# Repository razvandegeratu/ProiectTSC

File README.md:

Descrierea Funcționalității Hardware
Module și Interfețe

    Microcontroller: nRF52840 gestionează procesarea centrală.

    Display E-Paper: Comunică prin interfața SPI. S-a ales acest tip de ecran datorită consumului de energie zero în stare statică.

    Senzor IMU: Conectat prin I2C, utilizat pentru detectarea mișcării și orientării.

    Sistem de alimentare: Include un circuit de încărcare pentru bateria Li-Po și convertoare DC/DC pentru a asigura pragurile de tensiune de 3.3V necesare componentelor digitale.

    Interfață Utilizator: Trei butoane mecanice pentru navigare și un motor de vibrații pentru notificări haptice.

## Bill of Materials (BOM)

|Component|JLC Part #|Package|Description|Datasheet|
| :--- | :--- | :--- | :--- | :--- |
|C23, C27, C34, C42|[C21012218](https://www.lcsc.com/product-detail/C21012218.html)|-|Check availability|[datasheet](https://jlc-prod-smt.oss-eu-central-1.aliyuncs.com/smtDataManualFile/8603520985945550848-C21012218.pdf?response-content-disposition=attachment%3B%20filename%3DC21012218.pdf%3B%20filename%2A%3DUTF-8%27%27C21012218.pdf&x-oss-date=20260407T205848Z&x-oss-expires=1800&x-oss-security-token=CAISgAN1q6Ft5B2yfSjIr5r9Dd2HhJt1xpCRZnzhgHQ0Psp9nrTKiTz2IHhMdHJsAOodtv0%2FmmhT6PkclqRLcbhpcmfjV%2BZHzLB8qYoRtS1%2F4J7b16cNrbH4M4H6aXeirtuwDsz9SNTCALjPD3nPii50x5bjaDymRCbLGJaViJlhHLN1Ow6jdmhpCctxLAlvo9NgFxm3D%2Fu2NQPwiWf9FVdhvhEG6Vly8qOi2MaRmFy8yFTx0b0SvJ%2BjYMrmPctoN9JnSdC5mfdzau3a1TJ84gRD0a5wkaVA1zbDs5bfISEIuUzebreLqY03dV4mOvdqIcMe8qigz88fk%2FfIioH6xyxKOexoSCnFTOiiupCcQLPyao9jLu6iayqViY7QaIOTqQohZmkAMwVOasAsI3Ngh4zF97Qt0cVNkXO9gWfLI8DtuMleWoolCMBMoNHD0eS19jklBdzSlusJRAJJUVBflCeKEaRNSAd3WGhEfM2%2BBt4QT30w5N2u00S8OSMIfXAg5qKWD5sagAGsz%2FZUSUxHdlmxVPmipF%2FTcZWs78wlHh10XRuVSQAFwkjbrT5Hik%2Bt6g43igoBe9p%2FcAdU6beRw%2F0OV8Ul08RsL45K5wTZwHFsbzFcwqB3eAqV0VruhFdx%2FHGC73AK3f%2BS3e6Qh1%2F1xoEQbmetO%2F%2BEcdyt%2BmwKiZrCa5Agq9keuCAA&x-oss-signature-version=OSS4-HMAC-SHA256&x-oss-credential=STS.NYHFg3iDTqRzdZPdta2EQqqak%2F20260407%2Feu-central-1%2Foss%2Faliyun_v4_request&x-oss-signature=20ddec61a1b664f2d44439cb342bbd932d8702b658f2816e0dfb7eb77563430a)|
|R2_EP_DR, R9, R_PWR_EPD|[C3920633](https://www.lcsc.com/product-detail/C3920633.html)|0201|7.68k 0201 Thin Film Surface Mount Fixed Resistor +/-0.5% 0.031W CPF0201D7K68C1|[datasheet](https://wmsc.lcsc.com/wmsc/upload/file/pdf/v2/lcsc/2404081048_TE-Connectivity-CPF0201B511RE1_C3920633.pdf)|
|C1-EP-DR|[C9900156064](https://www.lcsc.com/product-detail/C9900156064.html)|201|Generic chip capacitor|[datasheet](https://ds.yuden.co.jp/TYCOMPAS/or/download?pn=MLAST063SCG681JFNA01&fileType=CA)|
|C2-EP-DR|[C9900156064](https://www.lcsc.com/product-detail/C9900156064.html)|201|Generic chip capacitor|[datasheet](https://ds.yuden.co.jp/TYCOMPAS/or/download?pn=MLAST063SCG681JFNA01&fileType=CA)|
|C11|[C9900156064](https://www.lcsc.com/product-detail/C9900156064.html)|201|Generic chip capacitor|[datasheet](https://ds.yuden.co.jp/TYCOMPAS/or/download?pn=MLAST063SCG681JFNA01&fileType=CA)|
|C24, C39|[C9900179830](https://www.lcsc.com/product-detail/C9900179830.html)|402|0402 (1005 Metric)|N/A|
|L2|[C12669](https://www.lcsc.com/product-detail/C12669.html)|402|Generic chip inductor|[datasheet](https://www.lcsc.com/datasheet/lcsc_datasheet_2304140030_Murata-Electronics-LQG15HS27NJ02D_C12669.pdf)|
|C1, C2, C17, C18|[C9900156064](https://www.lcsc.com/product-detail/C9900156064.html)|201|Generic chip capacitor|[datasheet](https://ds.yuden.co.jp/TYCOMPAS/or/download?pn=MLAST063SCG681JFNA01&fileType=CA)|
|L3|[C12669](https://www.lcsc.com/product-detail/C12669.html)|402|Generic chip inductor|[datasheet](https://www.lcsc.com/datasheet/lcsc_datasheet_2304140030_Murata-Electronics-LQG15HS27NJ02D_C12669.pdf)|
|C3, C4|[C9900156064](https://www.lcsc.com/product-detail/C9900156064.html)|201|Generic chip capacitor|[datasheet](https://ds.yuden.co.jp/TYCOMPAS/or/download?pn=MLAST063SCG681JFNA01&fileType=CA)|
|SJ1|N/A|Solder Jumper (Copper feature - leave open)|SMD solder JUMPER|N/A|
|C29, C30, C31, C32, C37, C38|[C3920633](https://www.lcsc.com/product-detail/C3920633.html)|0201|7.68k 0201 Thin Film Surface Mount Fixed Resistor +/-0.5% 0.031W CPF0201D7K68C1|[datasheet](https://wmsc.lcsc.com/wmsc/upload/file/pdf/v2/lcsc/2404081048_TE-Connectivity-CPF0201B511RE1_C3920633.pdf)|
|EPD_C1, EPD_C2, EPD_C6, EPD_C7, EPD_C8, EPD_C9, EPD_C10, EPD_C11, EPD_C12|[C9900156064](https://www.lcsc.com/product-detail/C9900156064.html)|201|Generic chip capacitor|[datasheet](https://ds.yuden.co.jp/TYCOMPAS/or/download?pn=MLAST063SCG681JFNA01&fileType=CA)|
|SW_DN, SW_ENT, SW_UP|[C569760](https://www.lcsc.com/product-detail/C569760.html)|SMD,3.9x2.9mm|-40℃~+85℃ 1.6N 1.6mm 15V 2.9mm 20mA 3.9mm 500,000 Cycles IP67 J-Lead Rectangular Button SPST Surface Mount,Vertical White With Bracket SMD,3.9x2.9mm Tactile Switches ROHS|[datasheet](https://wmsc.lcsc.com/wmsc/upload/file/pdf/v2/lcsc/2301111010_PANASONIC-EVPAKE31A_C569760.pdf)|
|Q1|[C2564](https://www.lcsc.com/product-detail/C2564.html)|TO-220AB|-55℃~+175℃ 1 P-Channel 180nC@10V 200W 20mΩ@10V 3.4nF 4V 55V 640pF 74A P-Channel TO-220AB MOSFETs ROHS|[datasheet](https://www.lcsc.com/datasheet/lcsc_datasheet_1809041724_Infineon-Technologies-IRF4905PBF_C2564.pdf)|
|C25, C33|[C9900179830](https://www.lcsc.com/product-detail/C9900179830.html)|402|0402 (1005 Metric)|N/A|
|ANT1|[C2917717](https://www.lcsc.com/product-detail/C2917717.html)|1206|-45℃~+125℃ 0.5dBi 1.3mm 1.6mm 100MHz 2.45GHz 2W 3.2mm 50Ω Patch Antenna 1206 Antennas ROHS|[datasheet](https://www.lcsc.com/datasheet/lcsc_datasheet_2404021210_Johanson-Dielectrics-2450AT18B100E_C2917717.pdf)|
|L1|[C12669](https://www.lcsc.com/product-detail/C12669.html)|402|Generic chip inductor|[datasheet](https://www.lcsc.com/datasheet/lcsc_datasheet_2304140030_Murata-Electronics-LQG15HS27NJ02D_C12669.pdf)|
|X2|[C32346](https://www.lcsc.com/product-detail/C32346.html)|SMD3215-2P|-40℃~+85℃ 12.5pF 32.768kHz 70kΩ Crystal Oscillator ±20ppm SMD3215-2P Crystals ROHS|[datasheet](https://www.lcsc.com/datasheet/lcsc_datasheet_2404180925_Seiko-Epson-Q13FC13500004_C32346.pdf)|
|X1|[C9009](https://www.lcsc.com/product-detail/C9009.html)|SMD3225-4P|-40℃~+85℃ 12pF 32MHz Crystal Oscillator ±10ppm ±20ppm SMD3225-4P Crystals ROHS|[datasheet](https://www.lcsc.com/datasheet/lcsc_datasheet_2403291504_YXC-Crystal-Oscillators-X322532MOB4SI_C9009.pdf)|
|R17, R18|[C3920633](https://www.lcsc.com/product-detail/C3920633.html)|0201|7.68k 0201 Thin Film Surface Mount Fixed Resistor +/-0.5% 0.031W CPF0201D7K68C1|[datasheet](https://wmsc.lcsc.com/wmsc/upload/file/pdf/v2/lcsc/2404081048_TE-Connectivity-CPF0201B511RE1_C3920633.pdf)|
|C43|[C9900156064](https://www.lcsc.com/product-detail/C9900156064.html)|201|Generic chip capacitor|[datasheet](https://ds.yuden.co.jp/TYCOMPAS/or/download?pn=MLAST063SCG681JFNA01&fileType=CA)|
|R1_EP_DR|[C3920633](https://www.lcsc.com/product-detail/C3920633.html)|0201|7.68k 0201 Thin Film Surface Mount Fixed Resistor +/-0.5% 0.031W CPF0201D7K68C1|[datasheet](https://wmsc.lcsc.com/wmsc/upload/file/pdf/v2/lcsc/2404081048_TE-Connectivity-CPF0201B511RE1_C3920633.pdf)|
|C6, C14, C20, C21|[C9900156064](https://www.lcsc.com/product-detail/C9900156064.html)|201|Generic chip capacitor|[datasheet](https://ds.yuden.co.jp/TYCOMPAS/or/download?pn=MLAST063SCG681JFNA01&fileType=CA)|
|EPD_C5|[C9900156064](https://www.lcsc.com/product-detail/C9900156064.html)|201|Generic chip capacitor|[datasheet](https://ds.yuden.co.jp/TYCOMPAS/or/download?pn=MLAST063SCG681JFNA01&fileType=CA)|
|D3|[C2969755](https://www.lcsc.com/product-detail/C2969755.html)|SOT-23-6L|Low Cap. ESD Protection Auto SOT-23-6 STMicroelectronics USBLC6-2SC6Y, Dual Uni-Directional TVS Diode Array, 6-Pin SOT-23|[datasheet](https://wmsc.lcsc.com/wmsc/upload/file/pdf/v2/lcsc/2211080730_STMicroelectronics-USBLC6-2SC6Y_C2969755.pdf)|
|C16|[C9900156064](https://www.lcsc.com/product-detail/C9900156064.html)|201|Generic chip capacitor|[datasheet](https://ds.yuden.co.jp/TYCOMPAS/or/download?pn=MLAST063SCG681JFNA01&fileType=CA)|
|J1|[C122434](https://www.lcsc.com/product-detail/C122434.html)|SMD,P=0.5mm,Surface Mount，Right Angle|FFC & FPC Connectors 0.5mm FPC RA SMT Dual Contact 24Ckt|[datasheet](https://www.molex.com/content/dam/molex/molex-dot-com/products/automated/en-us/salesdrawingpdf/503/503480/5034802400_sd.pdf)|
|R1_USB, R2_USB|[C3920633](https://www.lcsc.com/product-detail/C3920633.html)|0201|7.68k 0201 Thin Film Surface Mount Fixed Resistor +/-0.5% 0.031W CPF0201D7K68C1|[datasheet](https://wmsc.lcsc.com/wmsc/upload/file/pdf/v2/lcsc/2404081048_TE-Connectivity-CPF0201B511RE1_C3920633.pdf)|
|L5|[C1329646](https://www.lcsc.com/product-detail/C1329646.html)|SMD,4.8x4.8mm|1.6A 1.6A 4.7uH 41.4mΩ AEC-Q200 ±30% SMD,4.8x4.8mm Power Inductors ROHS|[datasheet](https://wmsc.lcsc.com/wmsc/upload/file/pdf/v2/lcsc/2304140030_BOURNS-SRR4828A-4R7Y_C1329646.pdf)|
|C9|[C9900156064](https://www.lcsc.com/product-detail/C9900156064.html)|201|Generic chip capacitor|[datasheet](https://ds.yuden.co.jp/TYCOMPAS/or/download?pn=MLAST063SCG681JFNA01&fileType=CA)|
|IC3|[C189517](https://www.lcsc.com/product-detail/C189517.html)|LGA-12(2x2)|Accelerometers Triaxial low-g 12bit Acceleration Sensor|[datasheet](https://www.lcsc.com/datasheet/C189517.pdf)|
|R5, R7, R8|[C3920633](https://www.lcsc.com/product-detail/C3920633.html)|0201|7.68k 0201 Thin Film Surface Mount Fixed Resistor +/-0.5% 0.031W CPF0201D7K68C1|[datasheet](https://wmsc.lcsc.com/wmsc/upload/file/pdf/v2/lcsc/2404081048_TE-Connectivity-CPF0201B511RE1_C3920633.pdf)|
|IC1|[C3682423](https://www.lcsc.com/product-detail/C3682423.html)|DSBGA-8(1.1x1.6)|Charger IC Lithium Ion/Polymer, Lithium Iron Phosphate 8-DSBGA (1.6x1.1)|[datasheet](https://www.ti.com/cn/lit/ds/symlink/bq25180.pdf?ts=1775594237116)|
|IC2|[C81079](https://www.lcsc.com/product-detail/C81079.html)|DSBGA-9|Haptic Driver for ERM/LRA with Built-In Library and Smart Loop Architecture|[datasheet](https://www.ti.com/cn/lit/gpn/drv2605)|
|C5, C7, C8, C12, C19|[C9900156064](https://www.lcsc.com/product-detail/C9900156064.html)|201|Generic chip capacitor|[datasheet](https://ds.yuden.co.jp/TYCOMPAS/or/download?pn=MLAST063SCG681JFNA01&fileType=CA)|
|C15|[C9900156064](https://www.lcsc.com/product-detail/C9900156064.html)|201|Generic chip capacitor|[datasheet](https://ds.yuden.co.jp/TYCOMPAS/or/download?pn=MLAST063SCG681JFNA01&fileType=CA)|
|R_TYPE_SEL|[C3920633](https://www.lcsc.com/product-detail/C3920633.html)|0201|7.68k 0201 Thin Film Surface Mount Fixed Resistor +/-0.5% 0.031W CPF0201D7K68C1|[datasheet](https://wmsc.lcsc.com/wmsc/upload/file/pdf/v2/lcsc/2404081048_TE-Connectivity-CPF0201B511RE1_C3920633.pdf)|
|L7|[C5832368](https://www.lcsc.com/product-detail/C5832368.html)|1008|13mΩ 470nH 6.5A 7.5A ±20% 1008 Power Inductors ROHS|[datasheet](https://wmsc.lcsc.com/wmsc/upload/file/pdf/v2/lcsc/2306021632_cjiang--Changjiang-Microelectronics-Tech-FTC252012SR47MBCA_C5832368.pdf)|
|TP (Test Pads)|N/A|N/A|Test pad|N/A|
|J4|[C709357](https://www.lcsc.com/product-detail/C709357.html)|SMD|-40℃~+85℃ 1 10,000 cycles 16P 30V 3A 7.81mm Female Surface Mount, Right Angle Type-C SMD USB Connectors ROHS|[datasheet](https://www.lcsc.com/datasheet/lcsc_datasheet_2404191039_Shenzhen-Kinghelm-Elec-KH-TYPE-C-16P_C709357.pdf)|
|U2|[C2682616](https://www.lcsc.com/product-detail/C2682616.html)|DFN-8-EP(2x2)|-40℃~+85℃ 1 2.5V~4.5V 3uA I2C Lithium Battery DFN-8-EP(2x2) Battery Management ROHS|[datasheet](https://www.lcsc.com/datasheet/lcsc_datasheet_2410121738_Analog-Devices-Inc--Maxim-Integrated-MAX17048G-T10_C2682616.pdf)|
|D2, D4, D5|[C82046](https://www.lcsc.com/product-detail/C82046.html)|SOD-123|ON SEMICONDUCTOR - MBR0530 - DIODE, SCHOTTKY, 0.5A, 30V, SOD-123|[datasheet](https://www.lcsc.com/datasheet/lcsc_datasheet_2304140030_onsemi-MBR0530T1G_C82046.pdf)|
|C10, C13, C22|[C9900156064](https://www.lcsc.com/product-detail/C9900156064.html)|201|Generic chip capacitor|[datasheet](https://ds.yuden.co.jp/TYCOMPAS/or/download?pn=MLAST063SCG681JFNA01&fileType=CA)|
|U1|[C3606653](https://www.lcsc.com/product-detail/C3606653.html)|QFN-48(6x6)|nRF52840|[datasheet](https://www.lcsc.com/datasheet/C3606653.pdf)|
|IC9|[C7065276](https://www.lcsc.com/product-detail/C7065276.html)|WLCSP-15B(2.3x1.4)|Buck-Boost Regulator Positive Output Step-Up/Step-Down I2C DC-DC Controller IC 15-WL-CSP (BSC) (1.4x2.3)|[datasheet](https://wmsc.lcsc.com/wmsc/upload/file/pdf/v2/lcsc/2312271436_Richtek-Tech-RT6160AWSC_C7065276.pdf)|
|Q3|[C469327](https://www.lcsc.com/product-detail/C469327.html)|SOT-323|MOSFET N-Ch 30V 1.5A TrenchFET SC70 Vishay Si1308EDL-T1-GE3 N-channel MOSFET Transistor, 1.5 A, 30 V, 3-Pin SC-70|[datasheet](https://www.lcsc.com/datasheet/lcsc_datasheet_1912202016_Vishay-Intertech-SI1308EDL-T1-GE3_C469327.pdf)|
|J2|[C90533](https://www.lcsc.com/product-detail/C90533.html)|P=1mm|CABLE ADAPTER 6 POS|[datasheet](https://wmsc.lcsc.com/wmsc/upload/file/pdf/v2/lcsc/1810141506_LX-FFC6P1-0mm7CM_C90533.pdf)|

5. Design Log și Decizii Tehnice

    PCB Stackup: Placa are o grosime de 1mm
    Plan de masă: S-au implementat planuri de masă pe ambele straturi (Top și Bottom) legate prin Via Stitching pentru a minimiza zgomotul electromagnetic, în special în zona circuitului radio.

    Antenă: Zona de sub antenă a fost decupată complet de planul de masă pe toate straturile pentru a asigura performanța optimă a semnalului BLE.

    Erori DRC acceptate: S-au ignorat erorile de tip "Dimension" la butoane și mufa USB-C deoarece acestea sunt necesare pentru alinierea mecanică cu carcasa, conform specificațiilor.

    Componente: Toate rezistențele și condensatoarele de decuplare (100nF) au fost plasate în capsulă 0201 cât mai aproape de pinii IC-urilor.

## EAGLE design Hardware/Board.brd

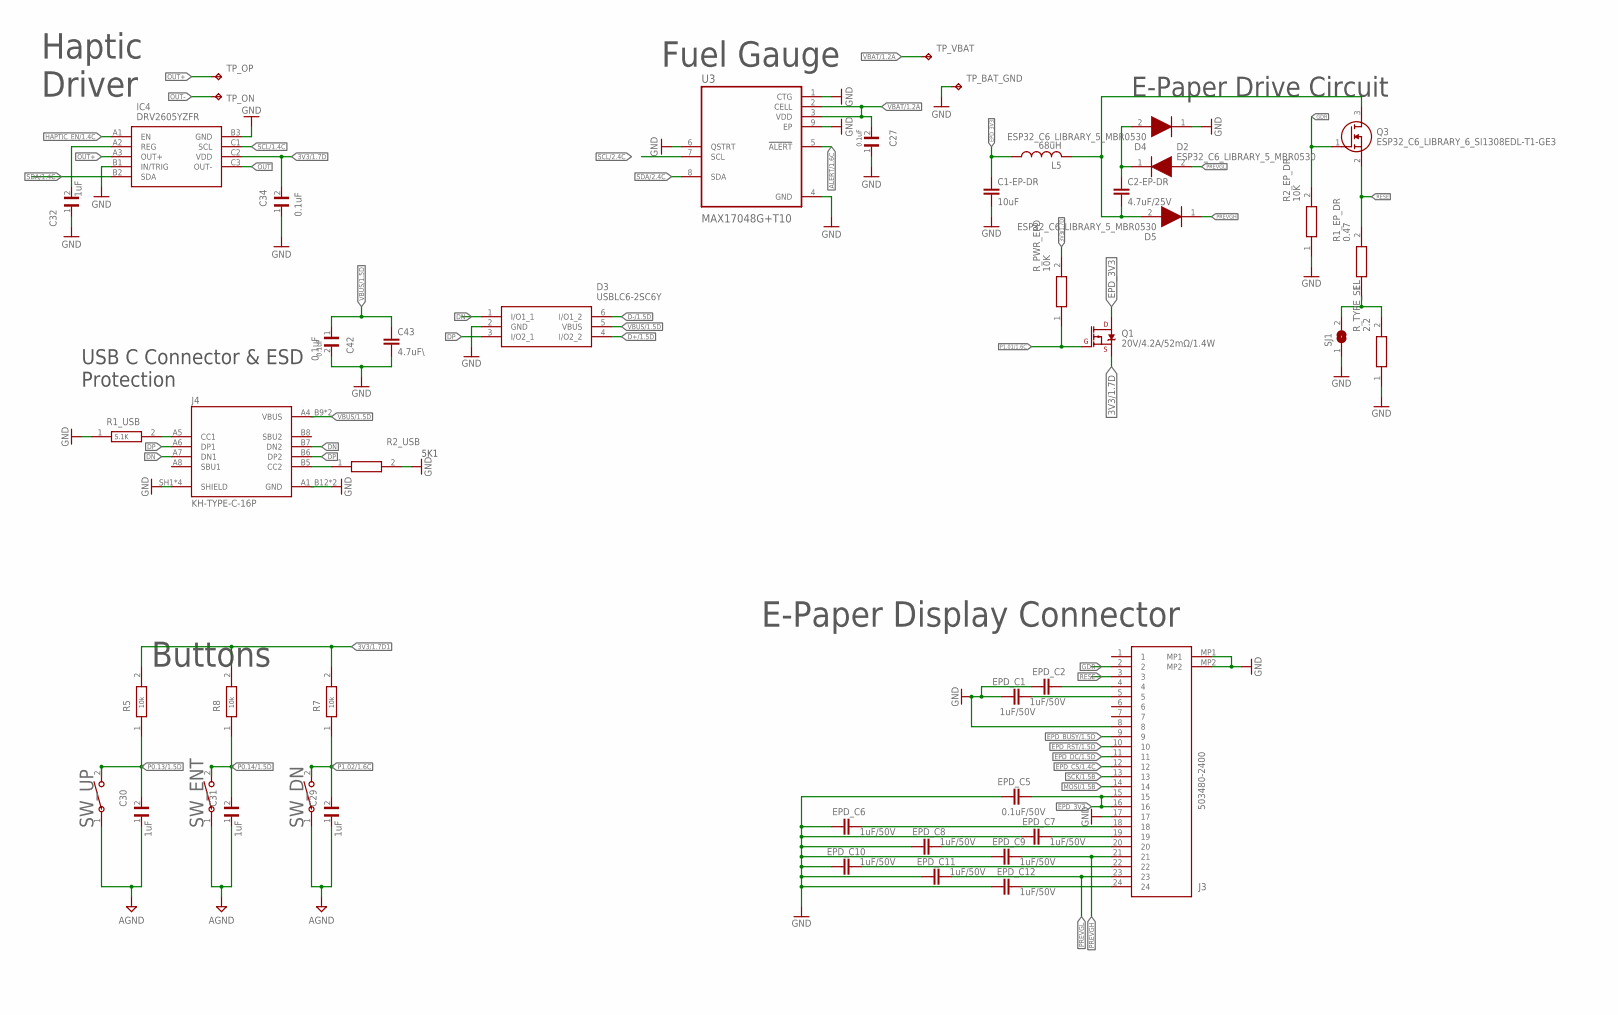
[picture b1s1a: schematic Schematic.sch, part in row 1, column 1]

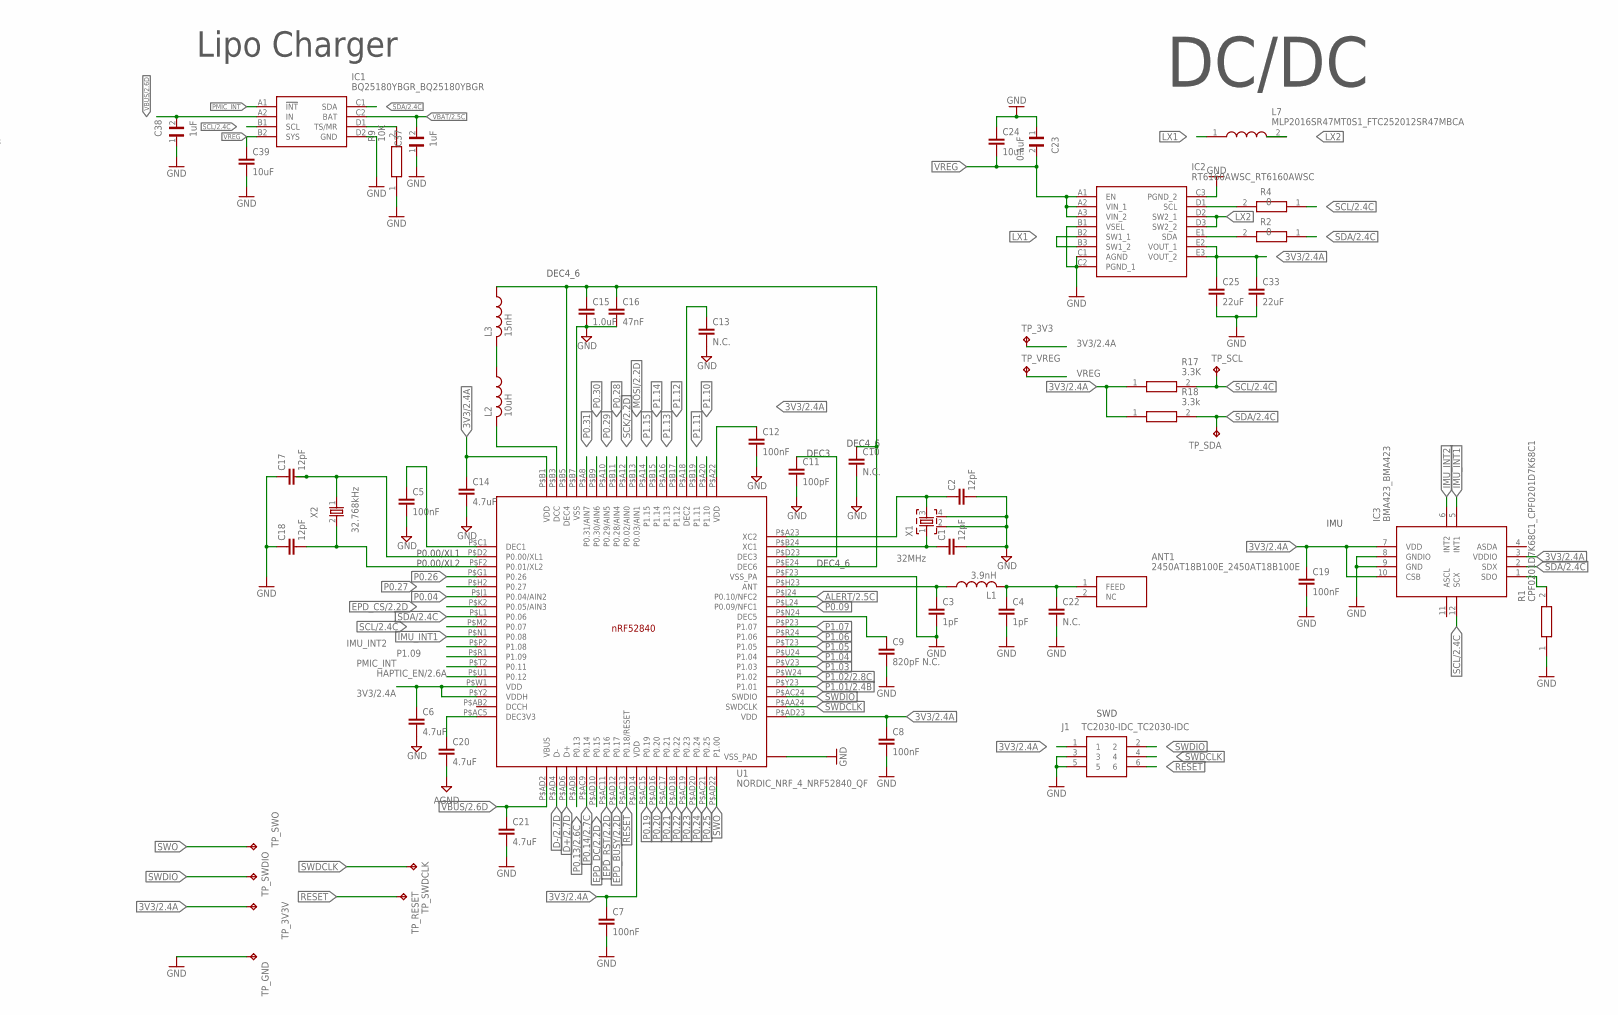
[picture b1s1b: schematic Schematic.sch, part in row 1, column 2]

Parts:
ANT1: 2450AT18B100E_2450AT18B100E; 2450AT18B100E_ANTC3216X140N
C1, C2, C17, C18: 12pF; NORDIC_NRF_3_RESC0201_L
C1-EP-DR, C24, C39: 10uF; NORDIC_NRF_3_RESC0402_L
C2-EP-DR: 4.7uF/25V; NORDIC_NRF_3_RESC0201_L
C3, C4: 1pF; NORDIC_NRF_3_RESC0201_L
C5, C7, C8, C12, C19: 100nF; NORDIC_NRF_3_RESC0201_L
C6, C20, C21: 4.7uF; NORDIC_NRF_3_RESC0402_L
C9: 820pF N.C.; NORDIC_NRF_3_RESC0201_L
C10, C13, C22: N.C.; NORDIC_NRF_3_RESC0201_L
C11: 100pF; NORDIC_NRF_3_RESC0201_L
C14: 4.7uF; 0402-TIGHT
C15: 1.0uF; 0402-TIGHT
C16: 47nF; NORDIC_NRF_3_RESC0201_L
C23, C42: 0.1uF; GRM011R60J152KE01L_2_CAPC0201X13N
C25, C33: 22uF; NORDIC_NRF_3_RESC0402_L
C27, C34: 0.1uF; GRM011R60J152KE01L_1_0201
C29, C30, C31, C37, C38: 1uF; GRM011R60J152KE01L_2_CAPC0201X13N
C32: 1uF; GRM011R60J152KE01L_1_0201
C43: 4.7uF\; NORDIC_NRF_3_RESC0402_L
D2, D4, D5: ESP32_C6_LIBRARY_5_MBR0530; ESP32_C6_LIBRARY_5_SOD3716X135N
D3: USBLC6-2SC6Y; ESP32_C6_LIBRARY_3_SOT95P280X145-6N
EPD_C1, EPD_C2, EPD_C6, EPD_C7, EPD_C8, EPD_C9, EPD_C10, EPD_C11, EPD_C12: 1uF/50V; NORDIC_NRF_3_RESC0402_L
EPD_C5: 0.1uF/50V; NORDIC_NRF_3_RESC0201_L
IC1: BQ25180YBGR_BQ25180YBGR; BQ25180YBGR_BGA8C40P2X4_100X155X50
IC2: RT6160AWSC_RT6160AWSC; RT6160AWSC_BGA15C40P3X5_140X230X60
IC3: BMA423_BMA423
IC4: DRV2605YZFR; DRV2605YZFR_BGA9C50P3X3_144X144X62
J1: TC2030-IDC_TC2030-IDC; TC2030-IDC_TC2030IDC
J3: 503480-2400; 503480-2400_5034802400
J4: KH-TYPE-C-16P; KH-TYPE-C-16P_KINGHELM_KH-TYPE-C-16P
L1: 3.9nH; NORDIC_NRF_2_RESC0402_L
L2: 10uH; NORDIC_NRF_2_RESC0402_L
L3: 15nH; NORDIC_NRF_2_RESC0402_L
L5: 68uH; NORDIC_NRF_2_RESC0402_L
L7: MLP2016SR47MT0S1_FTC252012SR47MBCA; MLP2016SR47MT0S1_INDC2016X100N
Q1: 20V/4.2A/52mΩ/1.4W; ESP32_C6_LIBRARY_4_ESP32_C6_LIBRARY_4_ESP32_C6_LIBRARY_4_ES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
Q3: ESP32_C6_LIBRARY_6_SI1308EDL-T1-GE3; ESP32_C6_LIBRARY_6_SOT65P210X110-3N
R1: CPF0201D7K68C1_CPF0201D7K68C1; CPF0201D7K68C1_0201
R1_EP_DR: 0.47; CPF0201D7K68C1_0201
R1_USB: 5.1K ohm; CPF0201D7K68C1_0201
R2, R4: 0; CPF0201D7K68C1_0201
R2_EP_DR, R5, R7, R8, R9: 10K; CPF0201D7K68C1_0201
R2_USB: 5.1K; CPF0201D7K68C1_0201
R17: 3.3K; ERA-1AEB3401C_0201
R18: 3.3k; ERA-1AEB3401C_0201
R_PWR_EPD: 10K; CPF0201D7K68C1_0201
R_TYPE_SEL: 2.2; CPF0201D7K68C1_0201
SJ1: ESP32_C6_LIBRARY_7_JUMPER_SJ
SW_DN: 2025-10-22_07-23-44_LIBRARY_EVP-AKE31ASW_EVP-AKE3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; 2025-10-22_07-23-44_LIBRARY_SW_EVP-AKE31A_PAN
SW_ENT: 2025-10-22_07-23-44_LIBRARY_EVP-AKE31ASW_EVP-AKE3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; 2025-10-22_07-23-44_LIBRARY_SW_EVP-AKE31A_PAN
SW_UP: 2025-10-22_07-23-44_LIBRARY_EVP-AKE31ASW_EVP-AKE3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; 2025-10-22_07-23-44_LIBRARY_SW_EVP-AKE31A_PAN
TP_3V3, TP_3V3V: HECTOR_WATCH_1_TPTP20R; HECTOR_WATCH_1_TP20R
TP_BAT_GND: HECTOR_WATCH_1_TPTP20R; HECTOR_WATCH_1_TP20R
TP_GND: HECTOR_WATCH_1_TPTP20R; HECTOR_WATCH_1_TP20R
TP_ON: HECTOR_WATCH_1_TPTP20R; HECTOR_WATCH_1_TP20R
TP_OP: HECTOR_WATCH_1_TPTP20R; HECTOR_WATCH_1_TP20R
TP_RESET: HECTOR_WATCH_1_TPTP20R; HECTOR_WATCH_1_TP20R
TP_SCL: HECTOR_WATCH_1_TPTP20R; HECTOR_WATCH_1_TP20R
TP_SDA: HECTOR_WATCH_1_TPTP20R; HECTOR_WATCH_1_TP20R
TP_SWDCLK: HECTOR_WATCH_1_TPTP20R; HECTOR_WATCH_1_TP20R
TP_SWDIO: HECTOR_WATCH_1_TPTP20R; HECTOR_WATCH_1_TP20R
TP_SWO: HECTOR_WATCH_1_TPTP20R; HECTOR_WATCH_1_TP20R
TP_VBAT: HECTOR_WATCH_1_TPTP20R; HECTOR_WATCH_1_TP20R
TP_VREG: HECTOR_WATCH_1_TPTP20R; HECTOR_WATCH_1_TP20R
U1: NORDIC_NRF_4_NRF52840_QF; NORDIC_NRF_4_AQFN50P700X700X85_HS-74N
U3: MAX17048G+T10; ESP32_C6_LIBRARY_SON50P200X200X80-9N
X1: 32MHz; NORDIC_NRF_BT-XTAL_2016_N
X2: 32.768kHz; NORDIC_NRF_1_XTAL_3215_N

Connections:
3V3/1.7D: C34.2, IC4.C2 (VDD), Q1.2 (S), R_PWR_EPD.2
3V3/1.7D1: R5.2, R7.2, R8.2
3V3/2.4A: C6.1, C7.1, C8.1, C12.1, C14.1, C19.1, C25.1, C33.1, IC2.E2 (VOUT_1), IC2.E3 (VOUT_2), IC3.3 (VDDIO), IC3.7 (VDD), IC3.10 (CSB), J1.1, R17.1, R18.1, TP_3V3.TP, TP_3V3V.TP, U1.P$A22 (VDD), U1.P$AD14 (VDD), U1.P$AD23 (VDD), U1.P$B1 (VDD), U1.P$W1 (VDD), U1.P$Y2 (VDDH)
ALERT/1.6C: U3.5 (!ALERT)
ALERT/2.5C: U1.P$J24 (P0.10/NFC2)
D+/1.5D: D3.4 (I/O2_2)
D+/2.7D: U1.P$AD6 (D+)
D-/1.5D: D3.6 (I/O1_2)
D-/2.7D: U1.P$AD4 (D-)
DN: D3.1 (I/O1_1), J4.A7 (DN1), J4.B7 (DN2)
DP: D3.3 (I/O2_1), J4.A6 (DP1), J4.B6 (DP2)
EPD_3V3: C1-EP-DR.1, EPD_C5.2, J3.15, J3.16, L5.1, Q1.3 (D)
EPD_BUSY/1.5D: J3.9
EPD_BUSY/2.2D: U1.P$AD12 (P0.17)
EPD_CS/1.4C: J3.12
EPD_CS/2.2D: U1.P$K2 (P0.05/AIN3)
EPD_DC/1.5D: J3.11
EPD_DC/2.2D: U1.P$AD10 (P0.15)
EPD_RST/1.5D: J3.10
EPD_RST/2.2D: U1.P$AC11 (P0.16)
GDR: J3.2, Q3.1 (G), R2_EP_DR.2
GND: C1.2, C1-EP-DR.2, C2.2, C3.2, C4.2, C5.2, C6.2, C7.2, C8.2, C9.2, C10.2, C11.2, C12.2, C13.2, C14.2, C15.2, C16.2, C17.1, C18.1, C19.2, C20.2, C21.2, C22.2, C23.1, C24.1, C25.2, C27.1, C29.1, C30.1, C31.1, C32.1, C33.2, C34.1, C37.1, C38.1, C39.2, C42.2, C43.2, D3.2 (GND), D4.1 (K), EPD_C1.1, EPD_C2.1, EPD_C5.1, EPD_C6.1, EPD_C7.1, EPD_C8.1, EPD_C9.1, EPD_C10.1, EPD_C11.1, EPD_C12.1, IC1.D2 (GND), IC2.B1 (VSEL), IC2.C1 (AGND), IC2.C2 (PGND_1), IC2.C3 (PGND_2), IC3.8 (GNDIO), IC3.9 (GND), IC4.B1 (IN/TRIG), IC4.B3 (GND), J1.3, J1.5, J3.8, J3.17, J3.MP1, J3.MP2, J4.A1_B12 (GND), J4.A12_B1 (GND), J4.SH1 (SHIELD), J4.SH2 (SHIELD), J4.SH3 (SHIELD), J4.SH4 (SHIELD), R1.1, R1_USB.1, R2_EP_DR.1, R2_USB.2, R9.1, R_TYPE_SEL.1, SJ1.1, SW_DN.1, SW_ENT.1, SW_UP.1, TP_BAT_GND.TP, TP_GND.TP, U1.P$74 (VSS_PAD), U1.P$75 (VSS_PAD), U1.P$76 (VSS_PAD), U1.P$77 (VSS_PAD), U1.P$78 (VSS_PAD), U1.P$79 (VSS_PAD), U1.P$80 (VSS_PAD), U1.P$81 (VSS_PAD), U1.P$82 (VSS_PAD), U1.P$83 (VSS_PAD), U1.P$84 (VSS_PAD), U1.P$85 (VSS_PAD), U1.P$86 (VSS_PAD), U1.P$87 (VSS_PAD), U1.P$88 (VSS_PAD), U1.P$89 (VSS_PAD), U1.P$90 (VSS_PAD), U1.P$B7 (VSS), U1.P$F23 (VSS_PA), U3.1 (CTG), U3.4 (GND), U3.6 (QSTRT), U3.9 (EP), X1.2, X1.4
HAPTIC_EN/1.4C: IC4.A1 (EN)
HAPTIC_EN/2.6A: U1.P$U1 (P0.12)
IMU_INT1: IC3.5 (INT1), U1.P$N1 (P0.08)
IMU_INT2: IC3.6 (INT2), U1.P$P2 (P1.08)
LX1: IC2.B2 (SW1_1), IC2.B3 (SW1_2), L7.1
LX2: IC2.D2 (SW2_1), IC2.D3 (SW2_2), L7.2
MOSI/1.5B: J3.14
MOSI/2.2D: U1.P$B13 (P0.03/AIN1)
unnamed: C20.1, U1.P$AC5 (DEC3V3)
unnamed: C18.2, U1.P$F2 (P0.01/XL2), X2.2
unnamed: L2.2, U1.P$B3 (DCC)
unnamed: L2.1, L3.2
unnamed: C1.1, U1.P$B24 (XC1), X1.1
unnamed: C13.1, U1.P$A18 (DEC2)
unnamed: C11.1, U1.P$D23 (DEC3)
unnamed: C10.1, C15.1, C16.1, L3.1, U1.P$B5 (DEC4), U1.P$E24 (DEC6)
unnamed: C17.2, U1.P$D2 (P0.00/XL1), X2.1
unnamed: C5.1, U1.P$C1 (DEC1)
unnamed: C2.1, U1.P$A23 (XC2), X1.3
unnamed: C3.1, L1.1, U1.P$H23 (ANT)
unnamed: ANT1.1 (FEED), C4.1, C22.1, L1.2
unnamed: IC1.D1 (TS/MR), R9.2
unnamed: C9.1, U1.P$N24 (DEC5)
unnamed: IC2.D1 (SCL), R4.2
unnamed: IC3.1 (SDO), R1.2
unnamed: C32.2, IC4.A2 (REG)
unnamed: J4.A5 (CC1), R1_USB.2
unnamed: IC2.E1 (SDA), R2.2
unnamed: C2-EP-DR.1, D2.1 (K), D4.2 (A)
unnamed: C2-EP-DR.2, D5.2 (A), L5.2, Q3.3 (D)
unnamed: R1_EP_DR.1, R_TYPE_SEL.2, SJ1.2
unnamed: J4.B5 (CC2), R2_USB.1
unnamed: EPD_C2.2, J3.4
unnamed: EPD_C1.2, J3.5
unnamed: EPD_C6.2, J3.18
unnamed: EPD_C7.2, J3.19
unnamed: EPD_C8.2, J3.20
unnamed: EPD_C10.2, J3.22
unnamed: EPD_C12.2, J3.24
OUT: IC4.C3 (OUT-)
OUT+: IC4.A3 (OUT+), TP_OP.TP
OUT-: TP_ON.TP
P0.04: U1.P$J1 (P0.04/AIN2)
P0.09: U1.P$L24 (P0.09/NFC1)
P0.13/1.5D: C30.2, R5.1, SW_UP.2
P0.13/2.6C: U1.P$AD8 (P0.13)
P0.14/1.5D: C31.2, R8.1, SW_ENT.2
P0.14/2.7C: U1.P$AC9 (P0.14)
P0.19: U1.P$AC15 (P0.19)
P0.20: U1.P$AD16 (P0.20)
P0.21: U1.P$AC17 (P0.21)
P0.22: U1.P$AD18 (P0.22)
P0.23: U1.P$AC19 (P0.23)
P0.24: U1.P$AD20 (P0.24)
P0.25: U1.P$AC21 (P0.25)
P0.26: U1.P$G1 (P0.26)
P0.27: U1.P$H2 (P0.27)
P0.28: U1.P$B11 (P0.28/AIN4)
P0.29: U1.P$A10 (P0.29/AIN5)
P0.30: U1.P$B9 (P0.30/AIN6)
P0.31: U1.P$A8 (P0.31/AIN7)
P1.01/1.6C: Q1.1 (G), R_PWR_EPD.1
P1.01/2.4B: U1.P$Y23 (P1.01)
P1.02/1.6C: C29.2, R7.1, SW_DN.2
P1.02/2.8C: U1.P$W24 (P1.02)
P1.03: U1.P$V23 (P1.03)
P1.04: U1.P$U24 (P1.04)
P1.05: U1.P$T23 (P1.05)
P1.06: U1.P$R24 (P1.06)
P1.07: U1.P$P23 (P1.07)
P1.09: U1.P$R1 (P1.09)
P1.10: U1.P$A20 (P1.10)
P1.11: U1.P$B19 (P1.11)
P1.12: U1.P$B17 (P1.12)
P1.13: U1.P$A16 (P1.13)
P1.14: U1.P$B15 (P1.14)
P1.15: U1.P$A14 (P1.15)
PMIC_INT: IC1.A1 (!INT), U1.P$T2 (P0.11)
PREVGH: D5.1 (K), EPD_C9.2, J3.21
PREVGL: D2.2 (A), EPD_C11.2, J3.23
RESE: J3.3, Q3.2 (S), R1_EP_DR.2
RESET: J1.6, TP_RESET.TP, U1.P$AC13 (P0.18/RESET)
SCK/1.5B: J3.13
SCK/2.2D: U1.P$A12 (P0.02/AIN0)
SCL/1.4C: IC4.C1 (SCL)
SCL/2.4C: IC1.B1 (SCL), IC3.12 (SCX), R4.1, R17.2, TP_SCL.TP, U1.P$M2 (P0.07), U3.7 (SCL)
SDA/1.4C: IC4.B2 (SDA)
SDA/2.4C: IC1.C1 (SDA), IC3.2 (SDX), R2.1, R18.2, TP_SDA.TP, U1.P$L1 (P0.06), U3.8 (SDA)
SWDCLK: J1.4, TP_SWDCLK.TP, U1.P$AA24 (SWDCLK)
SWDIO: J1.2, TP_SWDIO.TP, U1.P$AC24 (SWDIO)
SWO: TP_SWO.TP, U1.P$AD22 (P1.00)
VBAT/1.2A: C27.2, TP_VBAT.TP, U3.2 (CELL), U3.3 (VDD)
VBAT/2.5C: C37.2, IC1.C2 (BAT)
VBUS/1.5D: C42.1, C43.1, D3.5 (VBUS), J4.A4_B9 (VBUS), J4.A9_B4 (VBUS)
VBUS/2.6D: C21.1, C38.2, IC1.A2 (IN), U1.P$AD2 (VBUS)
VREG: C23.2, C24.2, C39.1, IC1.B2 (SYS), IC2.A1 (EN), IC2.A2 (VIN_1), IC2.A3 (VIN_2), TP_VREG.TP

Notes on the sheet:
SWD
Lipo Charger
DC/DC
Fuel Gauge
0.1uF
Haptic Driver
5.1K
5K1
USB C Connector & ESD Protection
E-Paper Display Connector
E-Paper Drive Circuit
Buttons
10k
IMU
DEC4_6
DEC3
P0.00/XL1
P0.00/XL2

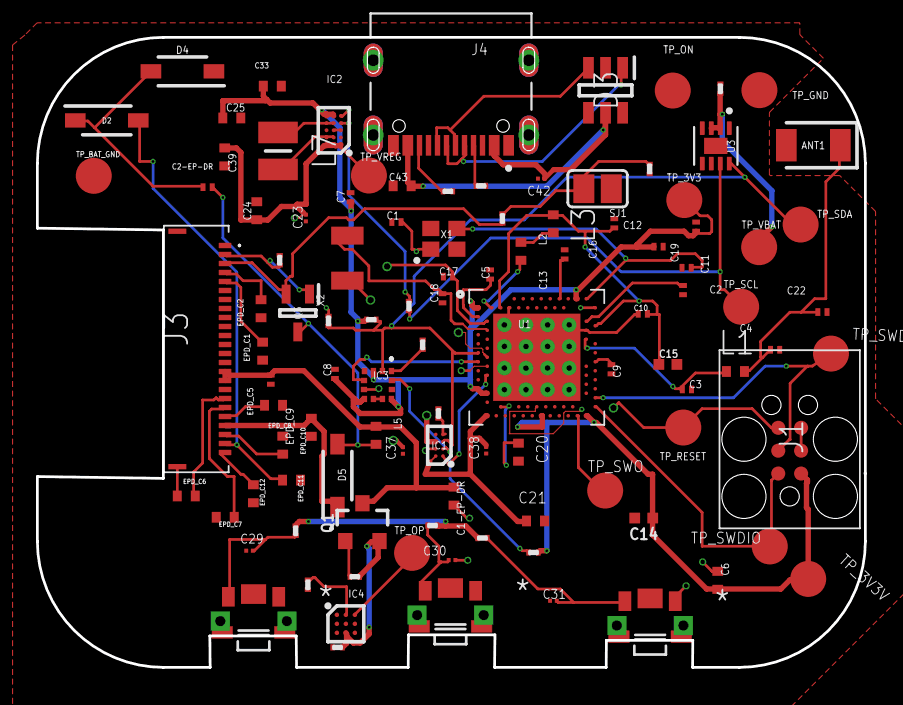
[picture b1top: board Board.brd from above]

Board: 4 copper layers, 46.0 x 35.0 mm, 105 parts (0 on the bottom side), 63 nets.

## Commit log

2026-04-10 Add files via upload
    Added sch, brd bom and cpl
2026-04-21 Add image to README.md
2026-04-21 Create LICENSE

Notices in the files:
parts and their libraries:
SparkFun-Capacitors: Licensing: Creative Commons ShareAlike 4.0 International - https://creativecommons.org/licenses/by-sa/4.0
COPYRIGHT: Copyright (C) 2025 Ultra Librarian. All rights reserved.
